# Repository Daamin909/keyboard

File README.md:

# Daamin's Keyboard - ShrekBoard

Made by [Daamin](https://daamin.tech)

Features:

- 78x keys!
- TKL Layout minus (9 keys above the arrow keys) and Fn moved to the bottom-left.
- 0.91" OLED for Pictures, Current - Playing Media etc
- EC11 Rotary Encoder - For Volume, Brightness etc
- Hack Club branded PCB 😎
- Raspberry Pico USB-C replacement: [Orpheus Pico](https://orpheuspico.hackclub.com/)
- Comfy Design
- KMK firmware

## PCB

The PCB's size is 360.4mm x 130.4mm

| Schematic                     |
| ----------------------------- |
|  |

| Front                     |
| ------------------------- |
|  |

| Back                     |
| ------------------------ |
|  |

| 3D - Front                   |
| ---------------------------- |
|  |

| 3D - Back                   |
| --------------------------- |
|  |

## Case

Thickness:-

- Top: 7mm
- Plate: 1.5mm
- Bottom: 11.5mm
- **Total**: 20mm

The case was made in Fusion360.

I chose to add branding on the bottom case only for aesthetics.
In order for the parts to be 3d printed, they're divided into 2 each.

# Top:

# Middle Plate:

# Bottom:

## 3D Render:

## Layout:

The Layout is a TKL (Tenkey-less) layout with some mods.

- removing Home, End etc island
- removing PrtSc etc island
- moving Fn key to bottom-left

## BOM

| Name                                                          | Qty | Final Price - INR (USD)         | Link                                                                                                       |
| ------------------------------------------------------------- | --- | ------------------------------- | ---------------------------------------------------------------------------------------------------------- |
| Gateron EF Grayish                                            | 80  | 1560 ($18.15)                   | [here](https://neomacro.in/products/gateron-ef-grayish)                                                    |
| Cherry Profile PBT Keycaps                                    | 1   | 1500 ($17.45)                   | [here](https://stackskb.com/store/black-and-yellow-keycaps/)                                               |
| Durock Smokey Screw-In Stabilizers V2 (4+1 w/ 6.25u spacebar) | 1   | 1595 ($18.55)                   | [here](https://stackskb.com/store/durock-smokey-screw-in-stabilizers-v2/)                                  |
| Diode 1N4148 Through - Hole                                   | 100 | 169 ($1.97)                     | [here](https://amzn.in/d/j3eLvoh)                                                                          |
| 0.91" OLED SSD1306                                            | 1   | 278 ($3.23)                     | [here](https://amzn.in/d/3cISYEV)                                                                          |
| EC11 Rotary Encoder                                           | 2   | 249 ($2.9)                      | [here](https://amzn.in/d/hVRxzij)                                                                          |
| M3 x 20mm Bolt                                                | 15  | 149 ($1.73)                     | [here](https://amzn.in/d/8GRQWAB)                                                                          |
| M3 Nuts                                                       | 8   | 108 ($1.26)                     | [here](https://amzn.in/d/7UQtsm8)                                                                          |
| M3 x 5mm Heatset Insert                                       | 25   | 246 ($2.86)                     | [here](https://amzn.in/d/ixybuAc)                                                                          |
| PCB - (Black Color)                                           | 1   | 3665.72 ($42.64)                | [here](https://hc-cdn.hel1.your-objectstorage.com/s/v3/c5fb1f15d2e06037b44047fc6c5d55dcc16f18ea_image.png) |
| Orpheus Pico                                                  | 1   | From HackClub HQ                |
| Rotary Encoder Knob                                           | 1   | From HackClub HQ                |
| Top Case - 1 (Black "./production/TOP1.step")                 | 1   | From HackClub HQ / Print Legion |
| Top Case - 2 (Black "./production/TOP2.step")                 | 1   | From HackClub HQ / Print Legion |
| Middle Plate - 1 (Black "./production/MIDDLE1.step")          | 1   | From HackClub HQ / Print Legion |
| Middle Plate - 2 (Black "./production/MIDDLE2.step")          | 1   | From HackClub HQ / Print Legion |
| Bottom Case - 1 (Black "./production/BOTTOM1.step")           | 1   | From HackClub HQ / Print Legion |
| Bottom Case - 2 (Black "./production/BOTTOM2.step")           | 1   | From HackClub HQ / Print Legion |

## Total Pricing

The keyboard comes out to be INR 9,519.72 ($110.73) when adding ordered parts and PCB. Does not include 3D - Printed case, Pico and Knob.
The PCB seems very costly when adding the shipping to India ($20), @qcoral please try to find alts for indians, or this is very very expensive.
PS:- (Seed Studio is $142 so thats not possible 💀)

## Notes :-

I want all the six 3D-printed parts to be printed in black color.
^ that includes: TOP1.step, TOP2.step, BOTTOM1.step, BOTTOM2.step, MIDDLE1.step and MIDDLE2.step
I want the 1x Rotary encoder knob as well.

Some of the above items, were ordered in packs due to unavailability of singular items.
2x extra switches, extra keycaps, extra nuts, bolts, heatsets, diodes, and one extra RE (can be used for my hackpad, if not sent from hackclub.)

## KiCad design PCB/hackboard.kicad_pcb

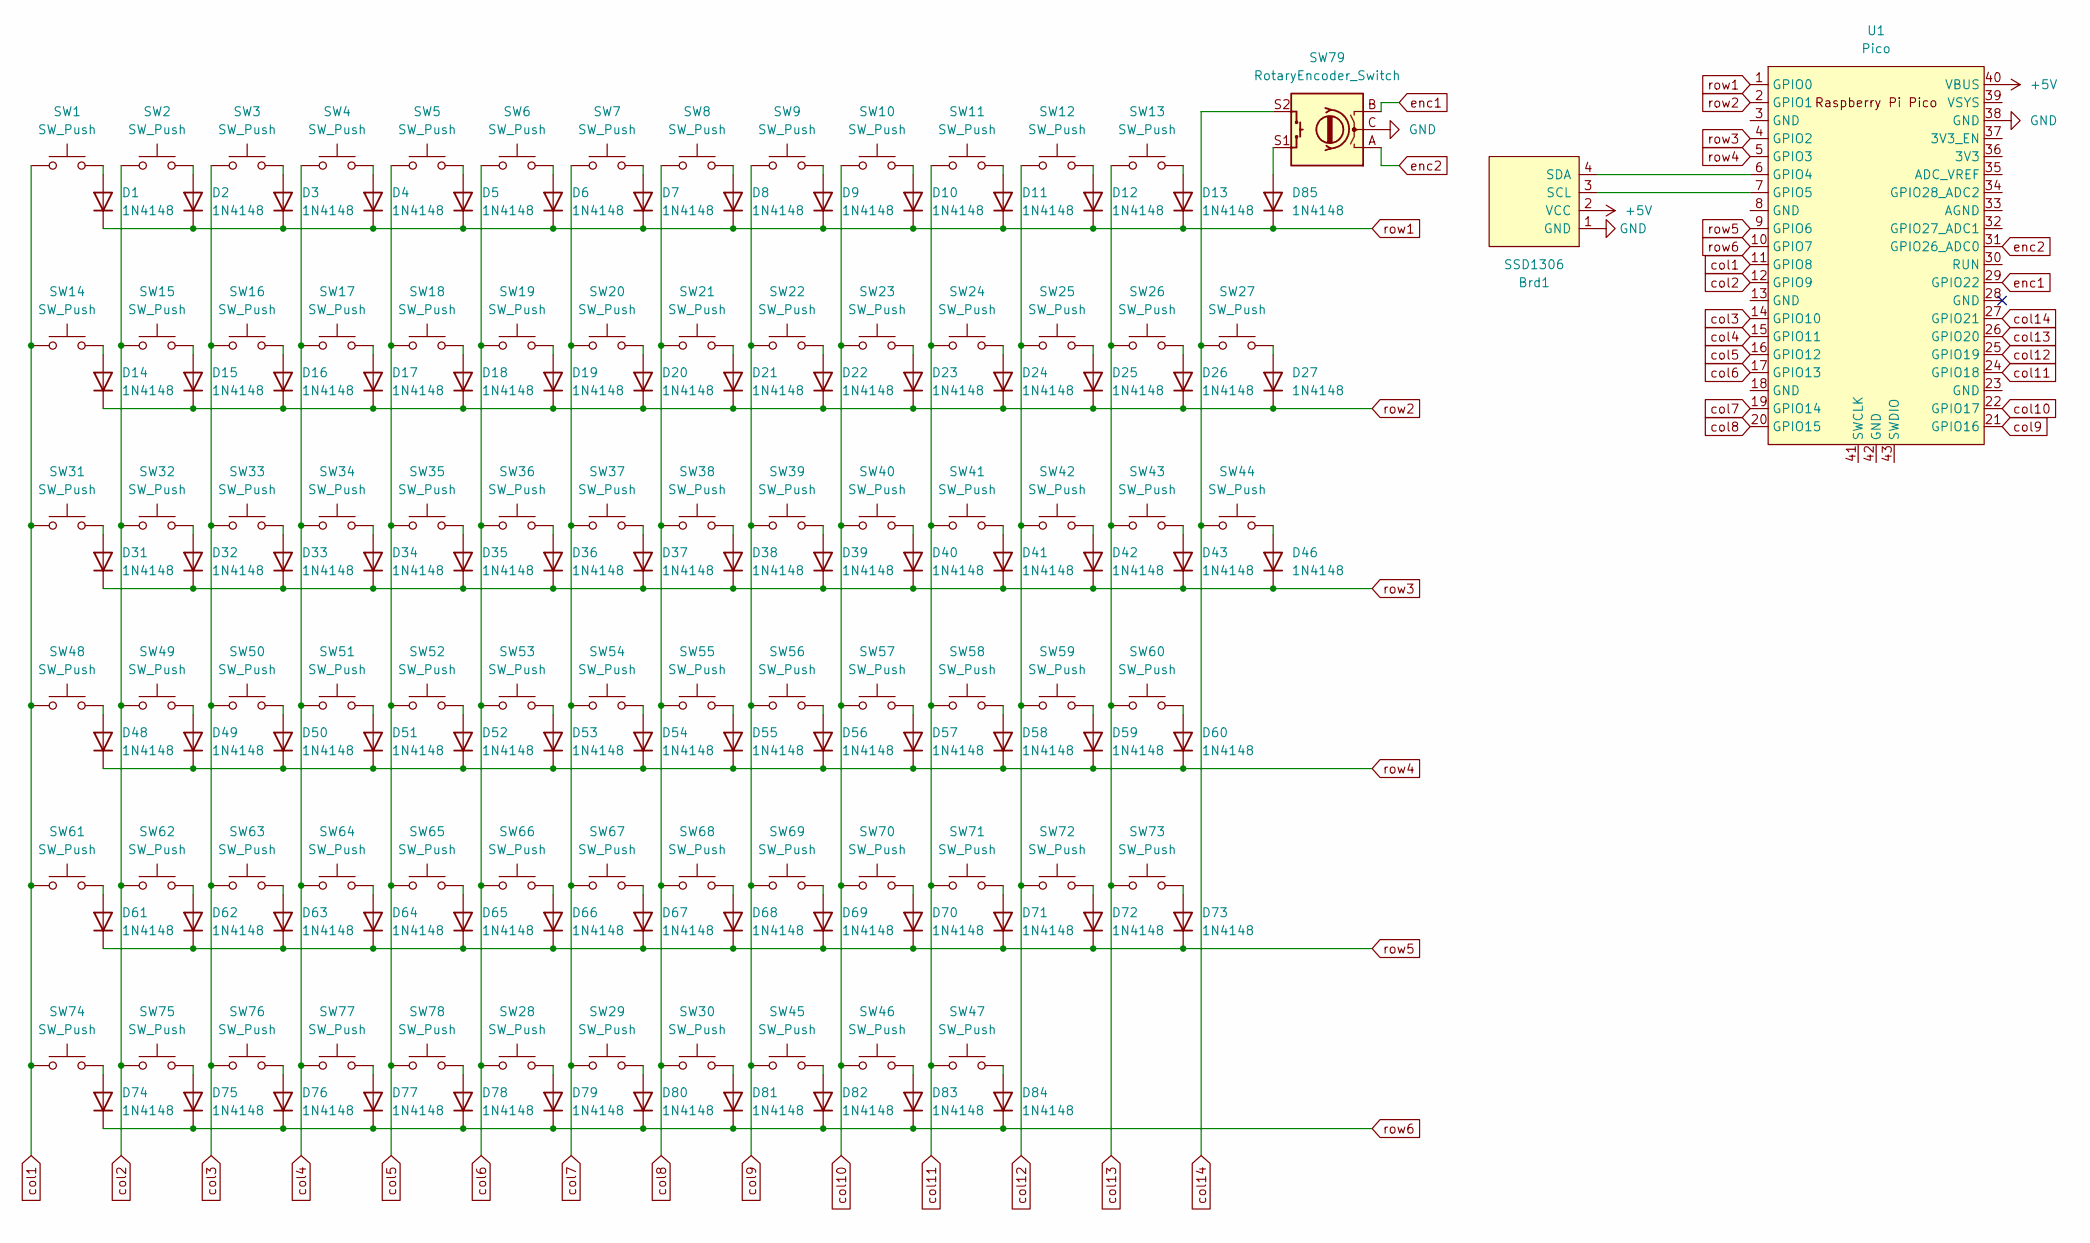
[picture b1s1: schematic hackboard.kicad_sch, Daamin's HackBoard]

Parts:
Brd1: SSD1306; SSD1306-0.91-OLED-4pin-128x32
D1, D2, D3, D4, D5, D6, D7, D8, D9, D10, D11, D12, D13, D14, D15, D16, D17, D18, D19, D20, D21, D22, D23, D24, D25, D26, D27, D31, D32, D33, D34, D35, D36, D37, D38, D39, D40, D41, D42, D43, D46, D48, D49, D50, D51, D52, D53, D54, D55, D56, D57, D58, D59, D60, D61, D62, D63, D64, D65, D66, D67, D68, D69, D70, D71, D72, D73, D74, D75, D76, D77, D78, D79, D80, D81, D82, D83, D84, D85: 1N4148; D_DO-35_SOD27_P7.62mm_Horizontal
SW1, SW2, SW3, SW4, SW5, SW6, SW7, SW8, SW9, SW10, SW11, SW12, SW13, SW14, SW15, SW16, SW17, SW18, SW19, SW20, SW21, SW22, SW23, SW24, SW25, SW26, SW32, SW33, SW34, SW35, SW36, SW37, SW38, SW39, SW40, SW41, SW42, SW43, SW45, SW46, SW47, SW49, SW50, SW51, SW52, SW53, SW54, SW55, SW56, SW57, SW58, SW59, SW62, SW63, SW64, SW65, SW66, SW67, SW68, SW69, SW70, SW71, SW73: SW_Push; SW_Cherry_MX_1.00u_PCB
SW27: SW_Push; SW_Cherry_MX_2.00u_PCB
SW28, SW29, SW30, SW74, SW75, SW76, SW77: SW_Push; SW_Cherry_MX_1.25u_PCB
SW31, SW44: SW_Push; SW_Cherry_MX_1.50u_PCB
SW48: SW_Push; SW_Cherry_MX_1.75u_PCB
SW60, SW61: SW_Push; SW_Cherry_MX_2.25u_PCB
SW72: SW_Push; SW_Cherry_MX_2.75u_PCB
SW78: SW_Push; SW_Cherry_MX_6.25u_PCB
SW79: RotaryEncoder_Switch; RotaryEncoder_Alps_EC11E-Switch_Vertical_H20mm_CircularMoun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
U1: Pico; RPi_Pico_SMD_TH

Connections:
+5V: Brd1.2 (VCC), U1.40 (VBUS)
GND: Brd1.1 (GND), SW79.C, U1.38 (GND)
unnamed: Brd1.3 (SCL), U1.7 (GPIO5)
unnamed: Brd1.4 (SDA), U1.6 (GPIO4)
unnamed: D1.2 (A), SW1.2
unnamed: D2.2 (A), SW2.2
unnamed: D3.2 (A), SW3.2
unnamed: D4.2 (A), SW4.2
unnamed: D5.2 (A), SW5.2
unnamed: D6.2 (A), SW6.2
unnamed: D7.2 (A), SW7.2
unnamed: D8.2 (A), SW8.2
unnamed: D9.2 (A), SW9.2
unnamed: D10.2 (A), SW10.2
unnamed: D11.2 (A), SW11.2
unnamed: D12.2 (A), SW12.2
unnamed: D13.2 (A), SW13.2
unnamed: D14.2 (A), SW14.2
unnamed: D15.2 (A), SW15.2
unnamed: D16.2 (A), SW16.2
unnamed: D17.2 (A), SW17.2
unnamed: D18.2 (A), SW18.2
unnamed: D19.2 (A), SW19.2
unnamed: D20.2 (A), SW20.2
unnamed: D21.2 (A), SW21.2
unnamed: D22.2 (A), SW22.2
unnamed: D23.2 (A), SW23.2
unnamed: D24.2 (A), SW24.2
unnamed: D25.2 (A), SW25.2
unnamed: D26.2 (A), SW26.2
unnamed: D27.2 (A), SW27.2
unnamed: D31.2 (A), SW31.2
unnamed: D32.2 (A), SW32.2
unnamed: D33.2 (A), SW33.2
unnamed: D34.2 (A), SW34.2
unnamed: D35.2 (A), SW35.2
unnamed: D36.2 (A), SW36.2
unnamed: D37.2 (A), SW37.2
unnamed: D38.2 (A), SW38.2
unnamed: D39.2 (A), SW39.2
unnamed: D40.2 (A), SW40.2
unnamed: D41.2 (A), SW41.2
unnamed: D42.2 (A), SW42.2
unnamed: D43.2 (A), SW43.2
unnamed: D46.2 (A), SW44.2
unnamed: D48.2 (A), SW48.2
unnamed: D49.2 (A), SW49.2
unnamed: D50.2 (A), SW50.2
unnamed: D51.2 (A), SW51.2
unnamed: D52.2 (A), SW52.2
unnamed: D53.2 (A), SW53.2
unnamed: D54.2 (A), SW54.2
unnamed: D55.2 (A), SW55.2
unnamed: D56.2 (A), SW56.2
unnamed: D57.2 (A), SW57.2
unnamed: D58.2 (A), SW58.2
unnamed: D59.2 (A), SW59.2
unnamed: D60.2 (A), SW60.2
unnamed: D61.2 (A), SW61.2
unnamed: D62.2 (A), SW62.2
unnamed: D63.2 (A), SW63.2
unnamed: D64.2 (A), SW64.2
unnamed: D65.2 (A), SW65.2
unnamed: D66.2 (A), SW66.2
unnamed: D67.2 (A), SW67.2
unnamed: D68.2 (A), SW68.2
unnamed: D69.2 (A), SW69.2
unnamed: D70.2 (A), SW70.2
unnamed: D71.2 (A), SW71.2
unnamed: D72.2 (A), SW72.2
unnamed: D73.2 (A), SW73.2
unnamed: D74.2 (A), SW74.2
unnamed: D75.2 (A), SW75.2
unnamed: D76.2 (A), SW76.2
unnamed: D77.2 (A), SW77.2
unnamed: D78.2 (A), SW78.2
unnamed: D79.2 (A), SW28.2
unnamed: D80.2 (A), SW29.2
unnamed: D81.2 (A), SW30.2
unnamed: D82.2 (A), SW45.2
unnamed: D83.2 (A), SW46.2
unnamed: D84.2 (A), SW47.2
unnamed: D85.2 (A), SW79.S1
col1: SW1.1, SW14.1, SW31.1, SW48.1, SW61.1, SW74.1, U1.11 (GPIO8)
col2: SW2.1, SW15.1, SW32.1, SW49.1, SW62.1, SW75.1, U1.12 (GPIO9)
col3: SW3.1, SW16.1, SW33.1, SW50.1, SW63.1, SW76.1, U1.14 (GPIO10)
col4: SW4.1, SW17.1, SW34.1, SW51.1, SW64.1, SW77.1, U1.15 (GPIO11)
col5: SW5.1, SW18.1, SW35.1, SW52.1, SW65.1, SW78.1, U1.16 (GPIO12)
col6: SW6.1, SW19.1, SW28.1, SW36.1, SW53.1, SW66.1, U1.17 (GPIO13)
col7: SW7.1, SW20.1, SW29.1, SW37.1, SW54.1, SW67.1, U1.19 (GPIO14)
col8: SW8.1, SW21.1, SW30.1, SW38.1, SW55.1, SW68.1, U1.20 (GPIO15)
col9: SW9.1, SW22.1, SW39.1, SW45.1, SW56.1, SW69.1, U1.21 (GPIO16)
col10: SW10.1, SW23.1, SW40.1, SW46.1, SW57.1, SW70.1, U1.22 (GPIO17)
col11: SW11.1, SW24.1, SW41.1, SW47.1, SW58.1, SW71.1, U1.24 (GPIO18)
col12: SW12.1, SW25.1, SW42.1, SW59.1, SW72.1, U1.25 (GPIO19)
col13: SW13.1, SW26.1, SW43.1, SW60.1, SW73.1, U1.26 (GPIO20)
col14: SW27.1, SW44.1, SW79.S2, U1.27 (GPIO21)
enc1: SW79.B, U1.29 (GPIO22)
enc2: SW79.A, U1.31 (GPIO26_ADC0)
row1: D1.1 (K), D2.1 (K), D3.1 (K), D4.1 (K), D5.1 (K), D6.1 (K), D7.1 (K), D8.1 (K), D9.1 (K), D10.1 (K), D11.1 (K), D12.1 (K), D13.1 (K), D85.1 (K), U1.1 (GPIO0)
row2: D14.1 (K), D15.1 (K), D16.1 (K), D17.1 (K), D18.1 (K), D19.1 (K), D20.1 (K), D21.1 (K), D22.1 (K), D23.1 (K), D24.1 (K), D25.1 (K), D26.1 (K), D27.1 (K), U1.2 (GPIO1)
row3: D31.1 (K), D32.1 (K), D33.1 (K), D34.1 (K), D35.1 (K), D36.1 (K), D37.1 (K), D38.1 (K), D39.1 (K), D40.1 (K), D41.1 (K), D42.1 (K), D43.1 (K), D46.1 (K), U1.4 (GPIO2)
row4: D48.1 (K), D49.1 (K), D50.1 (K), D51.1 (K), D52.1 (K), D53.1 (K), D54.1 (K), D55.1 (K), D56.1 (K), D57.1 (K), D58.1 (K), D59.1 (K), D60.1 (K), U1.5 (GPIO3)
row5: D61.1 (K), D62.1 (K), D63.1 (K), D64.1 (K), D65.1 (K), D66.1 (K), D67.1 (K), D68.1 (K), D69.1 (K), D70.1 (K), D71.1 (K), D72.1 (K), D73.1 (K), U1.9 (GPIO6)
row6: D74.1 (K), D75.1 (K), D76.1 (K), D77.1 (K), D78.1 (K), D79.1 (K), D80.1 (K), D81.1 (K), D82.1 (K), D83.1 (K), D84.1 (K), U1.10 (GPIO7)

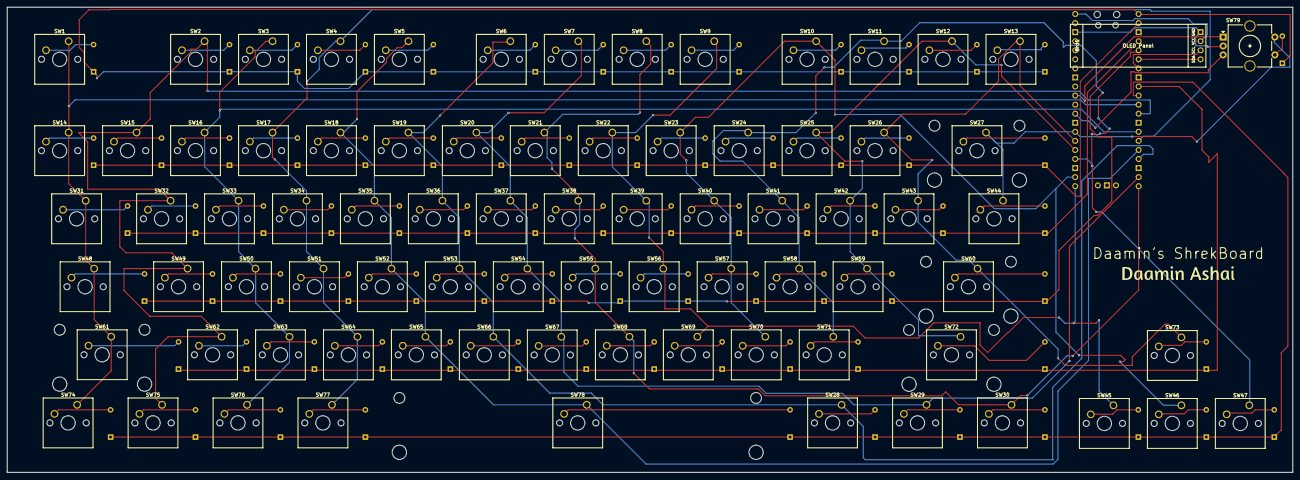
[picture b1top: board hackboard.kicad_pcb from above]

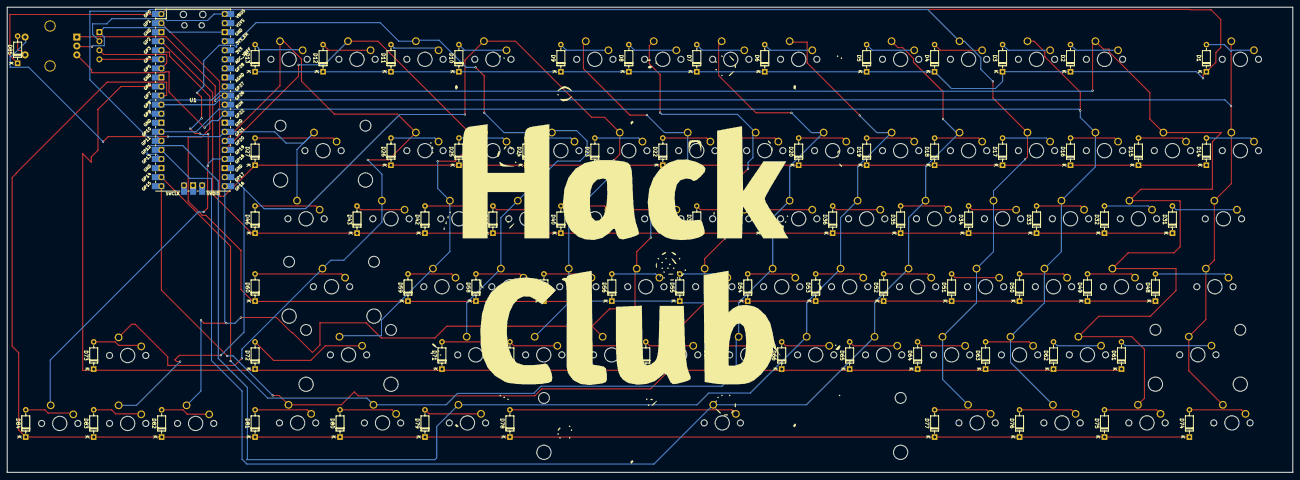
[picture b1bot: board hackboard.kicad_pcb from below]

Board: 2 copper layers, 360.4 x 130.4 mm, 160 parts (80 on the bottom side), 105 nets.

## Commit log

2025-02-25 added PCB, CAD and README
2025-02-25 re-export CAD and PCB
2025-02-26 updated PCB and assets
2025-03-03 updated Case and made padding thinner
2025-03-03 fix: incorrect image pat
2025-03-12 make keyboard thinner
2025-03-22 split case into 2, recompile STL and STEP files
2025-03-23 Added: New STL and Step files, gerbers, assets and README
2025-03-23 fix readme
